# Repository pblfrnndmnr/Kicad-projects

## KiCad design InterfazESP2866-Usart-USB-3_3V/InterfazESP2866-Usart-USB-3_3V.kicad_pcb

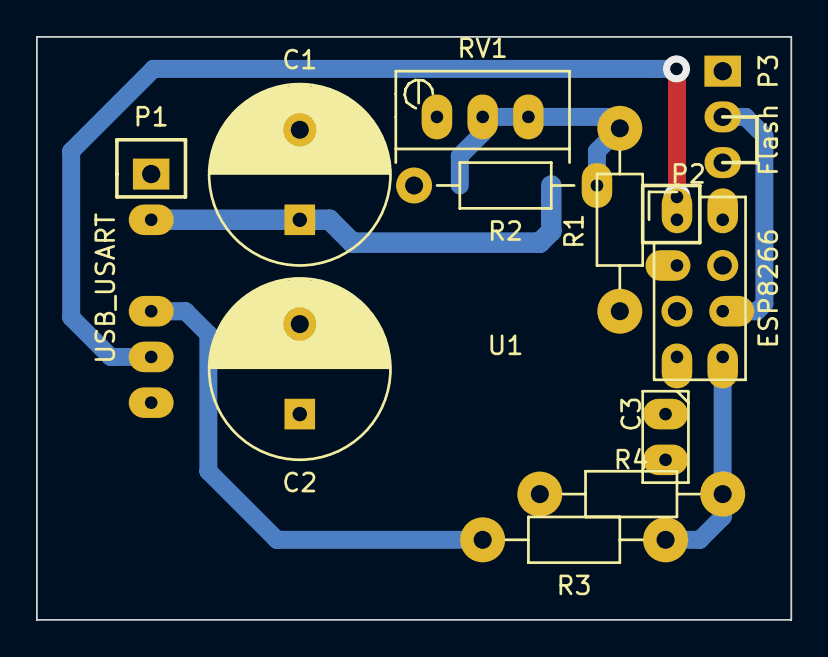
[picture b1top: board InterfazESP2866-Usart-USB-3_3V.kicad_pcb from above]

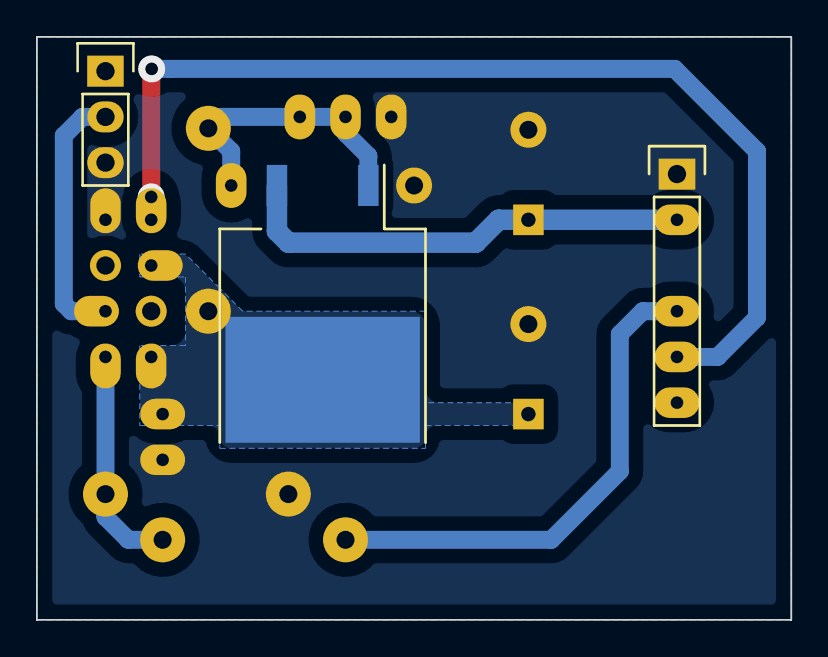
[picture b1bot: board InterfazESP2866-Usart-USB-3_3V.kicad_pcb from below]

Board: 2 copper layers, 41.9 x 32.4 mm, 12 parts (3 on the bottom side), 8 nets.

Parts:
C1: 10uF; C_Radial_D10_L13_P5
C2: 100uF; C_Radial_D10_L13_P5
C3: 100nF; C1
P1: USB_USART; Pin_Header_Straight_1x06
P2: ESP8266; Pin_Header_Straight_2x04
P3: Flash; Pin_Header_Straight_1x03
R1: 120; Resistor_Horizontal_RM10mm
R2: 330; Resistor_Horizontal_RM10mm
R3: 1k; Resistor_Horizontal_RM10mm
R4: 2k; Resistor_Horizontal_RM10mm
RV1: 1k; Potentiometer_Bourns_3296W_3-8Zoll_Inline_ScrewUp
U1: LM1084IS-ADJ/NOPB; TO-263-PadOut

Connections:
/CH_PD: C2.1, C3.1, P2.3, P2.7, R1.1, U1.2
/GPIO0: P2.6, P3.2
/RX: P2.8, R3.2, R4.1
/RXD_USB: P1.5, P2.1
/TXD_USB: P1.4, R3.1
/VCC_USB: C1.1, P1.2, U1.3
GND: C1.2, C2.2, C3.2, P1.1, P2.2, P3.3, R2.2, R4.2, RV1.1
unnamed: R1.2, R2.1, RV1.2, RV1.3, U1.1

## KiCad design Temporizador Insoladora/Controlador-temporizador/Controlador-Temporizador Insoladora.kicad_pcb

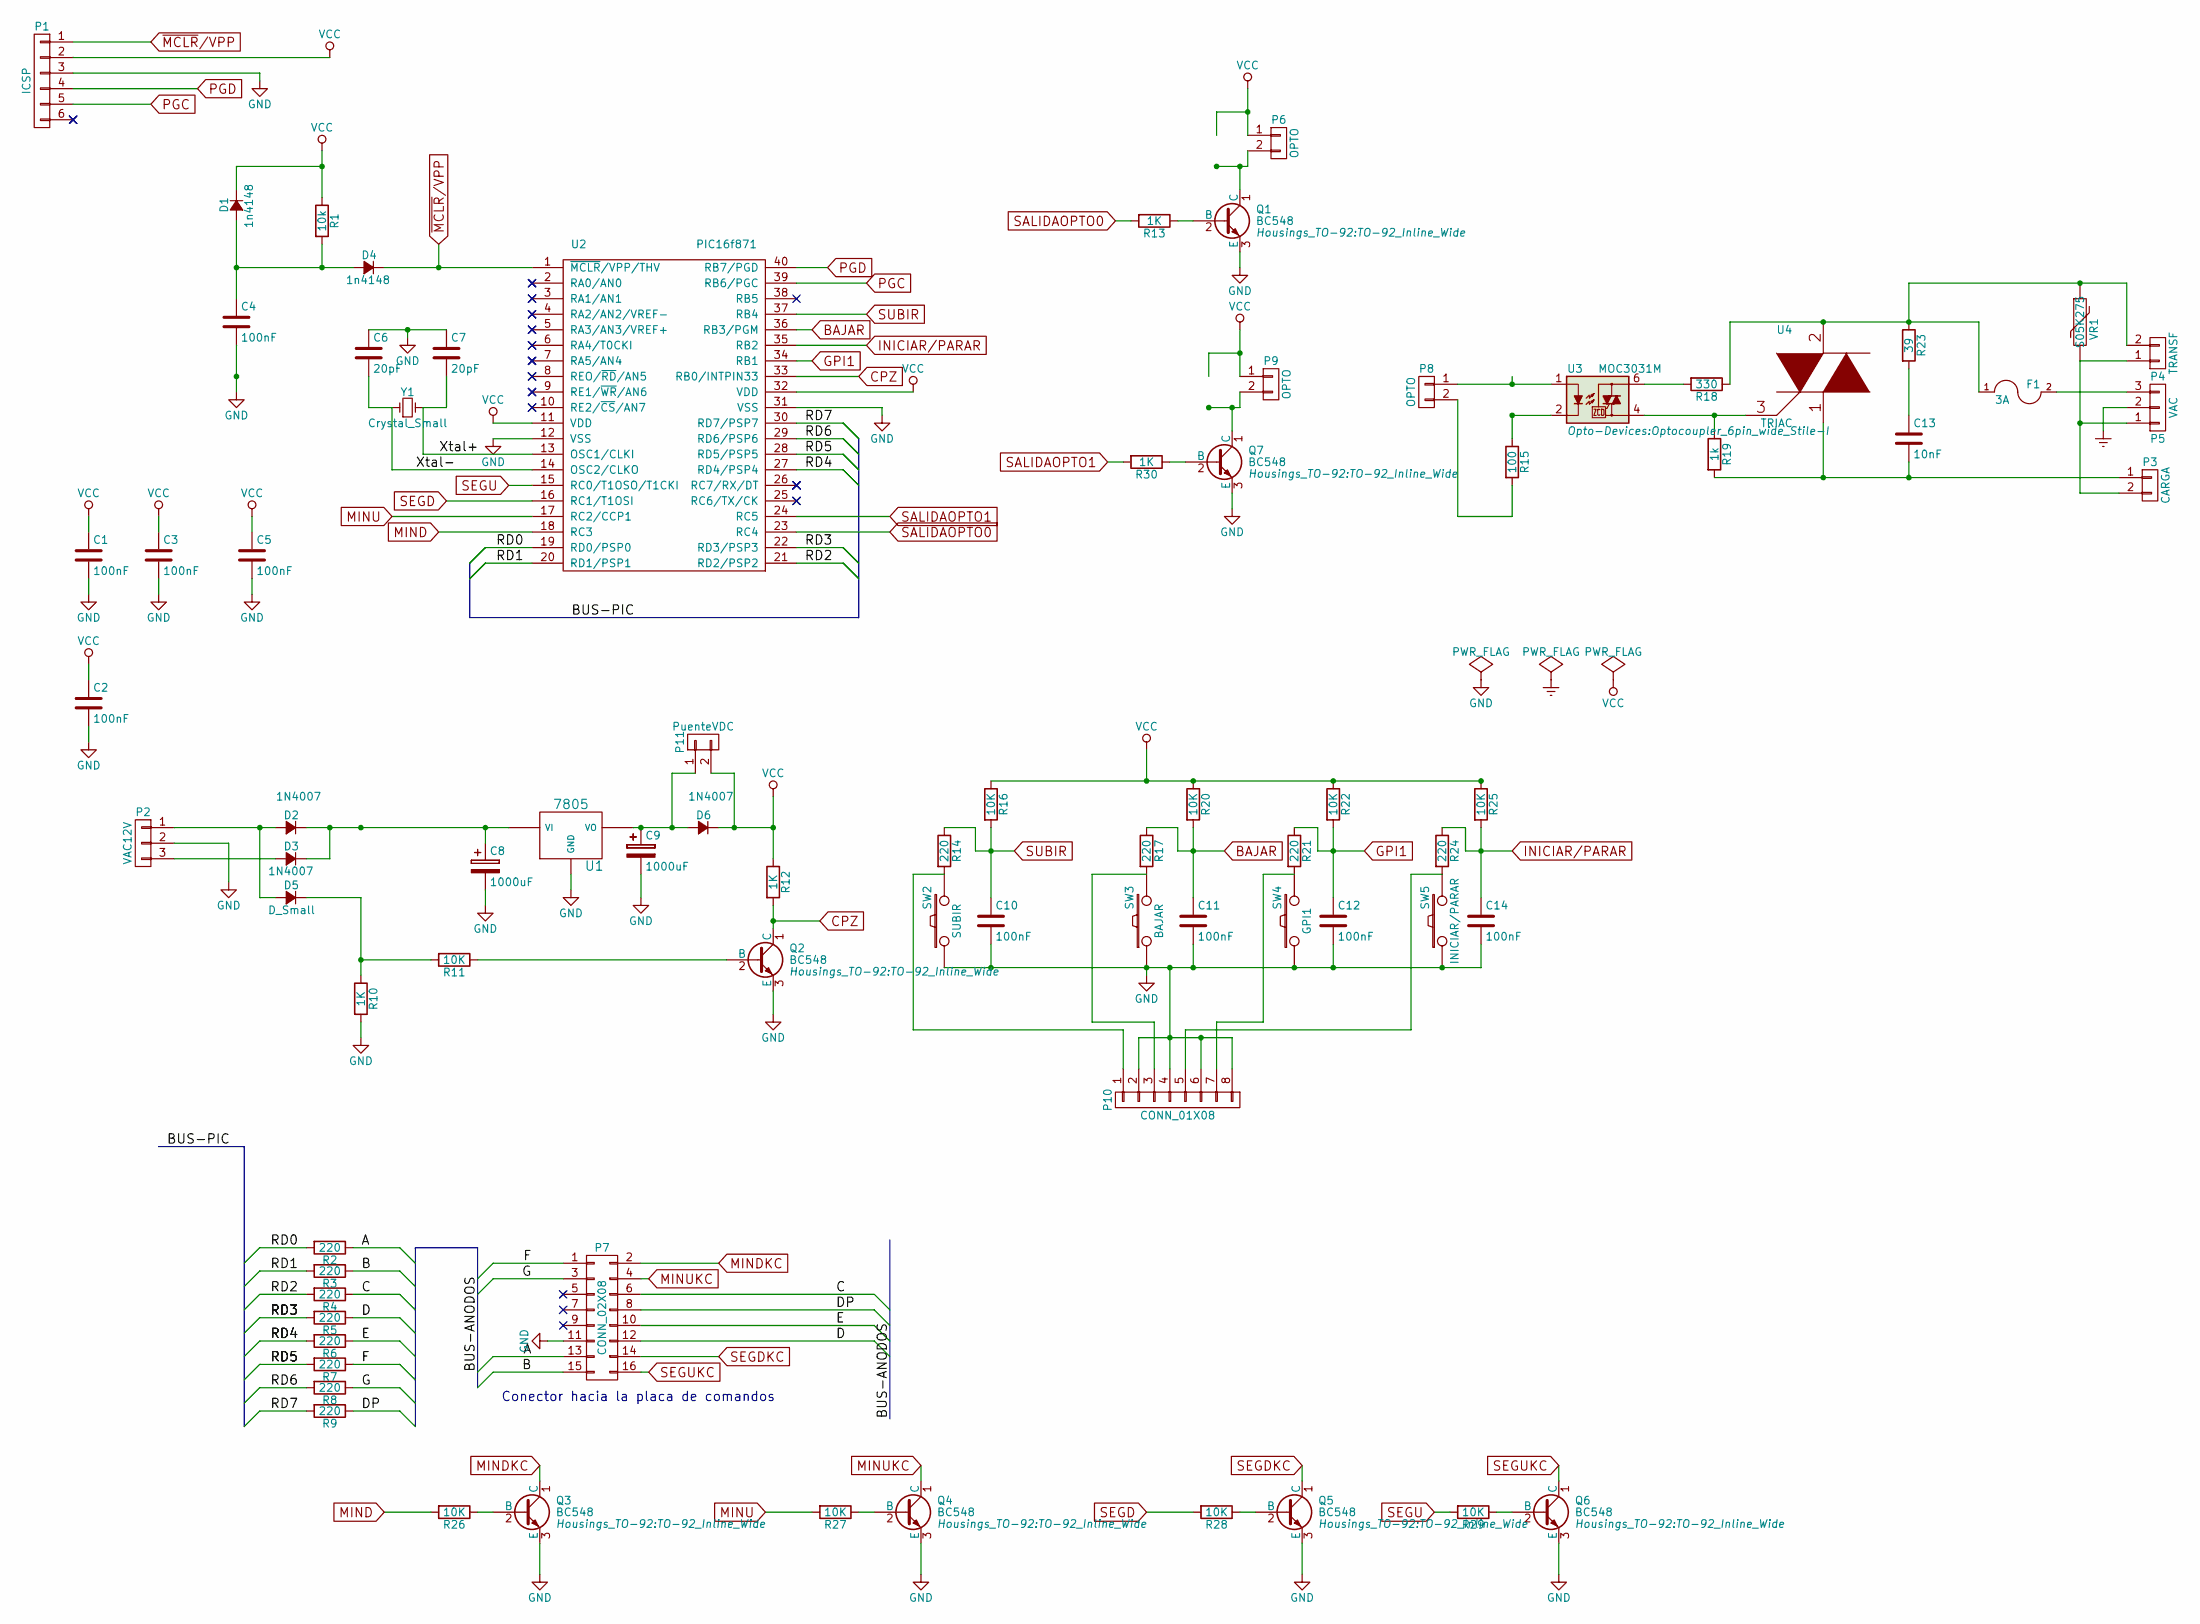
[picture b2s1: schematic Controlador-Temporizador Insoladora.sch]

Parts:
C1, C2, C3, C4, C5, C10, C11, C12, C14: 100nF; C_Rect_L4_W2.5_P2.5
C6, C7: 20pF; C_Rect_L4_W2.5_P2.5
C8, C9: 1000uF; C_Radial_D10_L16_P5
C13: 10nF; C_Rect_L13_W4_P10
D1, D4: 1n4148; Diode_DO-41_SOD81_Horizontal_RM10
D2, D3, D6: 1N4007; Diode_DO-41_SOD81_Horizontal_RM10
D5: D_Small; Diode_DO-41_SOD81_Horizontal_RM10
F1: 3A; Fuseholder5x20_horiz_open_lateral_Type-II
P1: ICSP; Pin_Header_Straight_1x06
P2: VAC12V; bornier3
P3: CARGA; bornier2
P4: TRANSF; bornier2
P5: VAC; bornier3
P6, P8, P9: OPTO; bornier2
P7: CONN_02X08; Socket_Strip_Straight_2x08
P10: CONN_01X08; Socket_Strip_Straight_1x08
P11: PuenteVDC; Socket_Strip_Straight_1x02
Q1, Q2, Q3, Q4, Q5, Q6, Q7: BC548; TO-92_Inline_Wide
R1: 10k; R3
R2, R3, R4, R5, R6, R7, R8, R9, R14, R17, R21, R24: 220; R3
R10, R12, R13, R30: 1K; R3
R11, R16, R20, R22, R25, R26, R27, R28, R29: 10K; R3
R15: 100; R3
R18: 330; R3
R19: 1k; R3
R23: 39; R3
SW2: SUBIR; SW_PUSH_SMALL
SW3: BAJAR; SW_PUSH_SMALL
SW4: GPI1; SW_PUSH_SMALL
SW5: INICIAR/PARAR; SW_PUSH_SMALL
U1: 7805; LM78XXV
U2: PIC16f871; DIP-40__600
U3: MOC3031M; Optocoupler_6pin_wide_Stile-I
U4: TRIAC; TO-220_Neutral123_Horizontal_LargePads
VR1: S05K275; C_Rect_L13_W4_P10
Y1: Crystal_Small; Crystal_HC50-U_Vertical

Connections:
/A: P7.13, R2.1
/B: P7.15, R3.1
/C: P7.6, R4.1
/D: P7.12, R5.1
/DP: P7.8, R9.1
/E: P7.10, R6.1
/F: P7.1, R7.1
/G: P7.3, R8.1
/RD0: R2.2, U2.19 (RD0/PSP0)
/RD1: R3.2, U2.20 (RD1/PSP1)
/RD2: R4.2, U2.21 (RD2/PSP2)
/RD3: R5.2, U2.22 (RD3/PSP3)
/RD4: R6.2, U2.27 (RD4/PSP4)
/RD5: R7.2, U2.28 (RD5/PSP5)
/RD6: R8.2, U2.29 (RD6/PSP6)
/RD7: R9.2, U2.30 (RD7/PSP7)
/Xtal+: C7.2, U2.13 (OSC1/CLKI), Y1.2
/Xtal-: C6.2, U2.14 (OSC2/CLKO), Y1.1
BAJAR: C11.1, R17.1, R20.2, U2.36 (RB3/PGM)
CPZ: Q2.1 (C), R12.2, U2.33 (RB0/INTPIN33)
Earth: P5.2
GND: C1.2, C2.2, C3.2, C4.2, C5.2, C6.1, C7.1, C8.2, C9.2, C10.2, C11.2, C12.2, C14.2, P1.3, P2.2, P7.11, P10.2, P10.4, P10.6, P10.8, Q1.3 (E), Q2.3 (E), Q3.3 (E), Q4.3 (E), Q5.3 (E), Q6.3 (E), Q7.3 (E), R10.2, SW2.1, SW3.1, SW4.1, SW5.1, U1.GND, U2.12 (VSS), U2.31 (VSS)
GPI1: C12.1, R21.1, R22.2, U2.34 (RB1)
INICIAR/PARAR: C14.1, R24.1, R25.2, U2.35 (RB2)
MIND: R26.2, U2.18 (RC3)
MINDKC: P7.2, Q3.1 (C)
MINU: R27.2, U2.17 (RC2/CCP1)
MINUKC: P7.4, Q4.1 (C)
unnamed: C4.1, D1.1 (A), D4.1 (A), R1.2
unnamed: C8.1, D2.2 (C), D3.2 (C), U1.VI
unnamed: C9.1, D6.1 (A), P11.1, U1.VO
unnamed: C13.1, R23.2
unnamed: C13.2, P3.1, R19.2, U4.1
unnamed: D2.1 (A), D5.1 (A), P2.1
unnamed: D3.1 (A), P2.3
unnamed: D5.2 (C), R10.1, R11.2
unnamed: F1.1, P4.2, R18.1, R23.1, U4.2, VR1.1
unnamed: F1.2, P5.3
unnamed: P3.2, P4.1, P5.1, VR1.2
unnamed: P6.2, Q1.1 (C)
unnamed: P8.1, U3.1
unnamed: P8.2, R15.2
unnamed: P9.2, Q7.1 (C)
unnamed: P10.1, R14.2, SW2.2
unnamed: P10.3, R17.2, SW3.2
unnamed: P10.5, R24.2, SW5.2
unnamed: P10.7, R21.2, SW4.2
unnamed: Q1.2 (B), R13.1
unnamed: Q2.2 (B), R11.1
unnamed: Q3.2 (B), R26.1
unnamed: Q4.2 (B), R27.1
unnamed: Q5.2 (B), R28.1
unnamed: Q6.2 (B), R29.1
unnamed: Q7.2 (B), R30.1
unnamed: R15.1, U3.2
unnamed: R18.2, U3.6
unnamed: R19.1, U3.4, U4.3
PGC: P1.5, U2.39 (RB6/PGC)
PGD: P1.4, U2.40 (RB7/PGD)
SALIDAOPTO0: R13.2, U2.23 (RC4)
SALIDAOPTO1: R30.2, U2.24 (RC5)
SEGD: R28.2, U2.16 (RC1/T1OSI)
SEGDKC: P7.14, Q5.1 (C)
SEGU: R29.2, U2.15 (RC0/T1OSO/T1CKI)
SEGUKC: P7.16, Q6.1 (C)
SUBIR: C10.1, R14.1, R16.2, U2.37 (RB4)
VCC: C1.1, C2.1, C3.1, C5.1, D1.2 (C), D6.2 (C), P1.2, P6.1, P9.1, P11.2, R1.1, R12.1, R16.1, R20.1, R22.1, R25.1, U2.11 (VDD), U2.32 (VDD)
~MCLR~/VPP: D4.2 (C), P1.1, U2.1 (~MCLR~/VPP/THV)

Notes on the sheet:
Conector hacia la placa de comandos

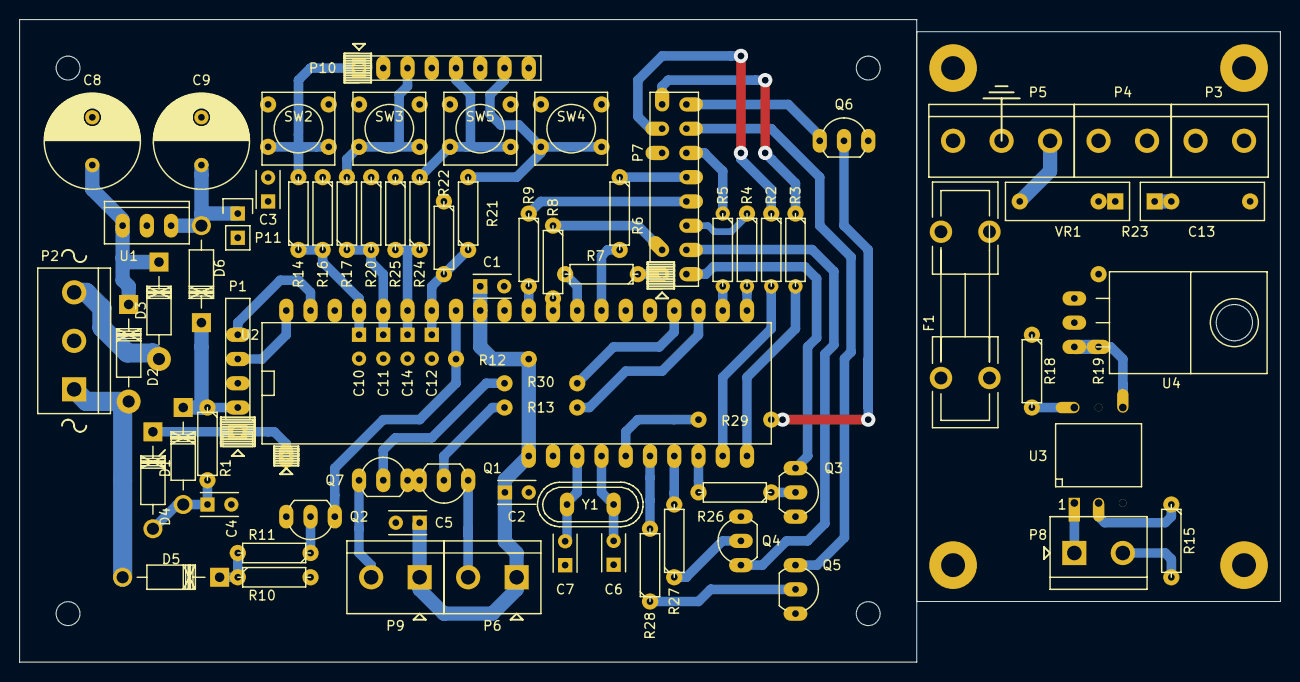
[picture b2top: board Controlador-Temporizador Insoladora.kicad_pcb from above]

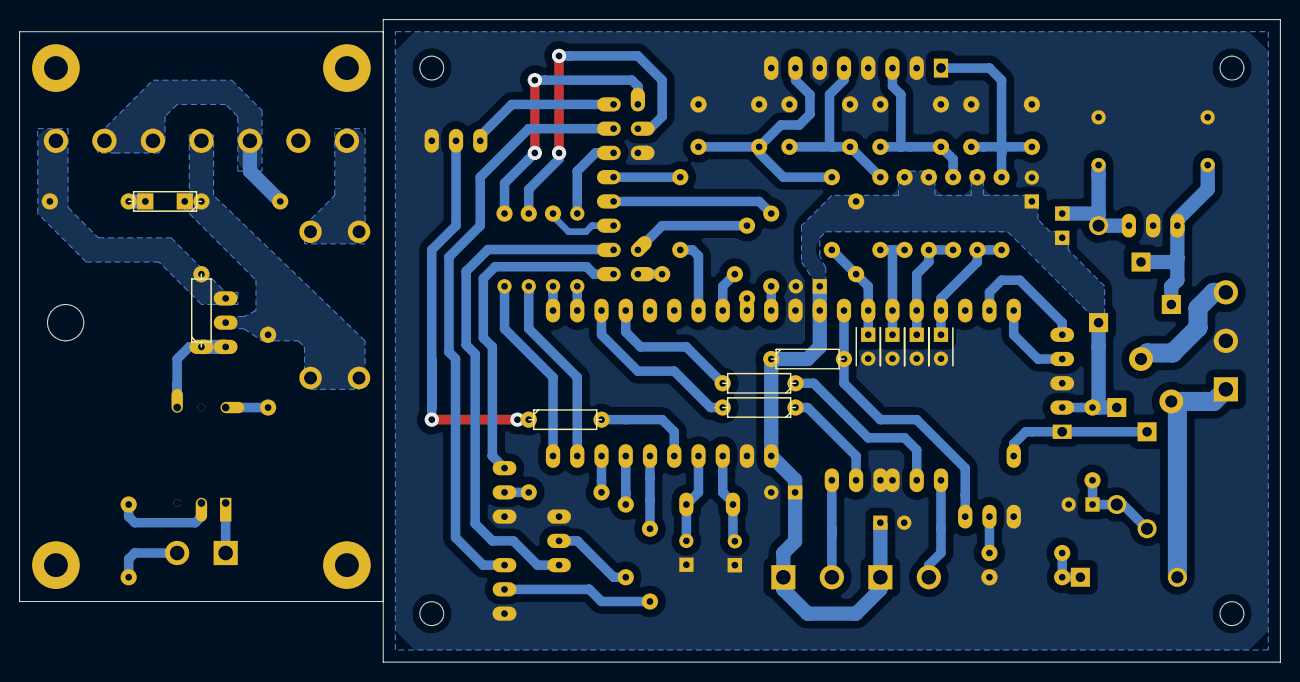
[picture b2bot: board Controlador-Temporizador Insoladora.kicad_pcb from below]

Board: 2 copper layers, 132.1 x 67.3 mm, 79 parts (10 on the bottom side), 67 nets.

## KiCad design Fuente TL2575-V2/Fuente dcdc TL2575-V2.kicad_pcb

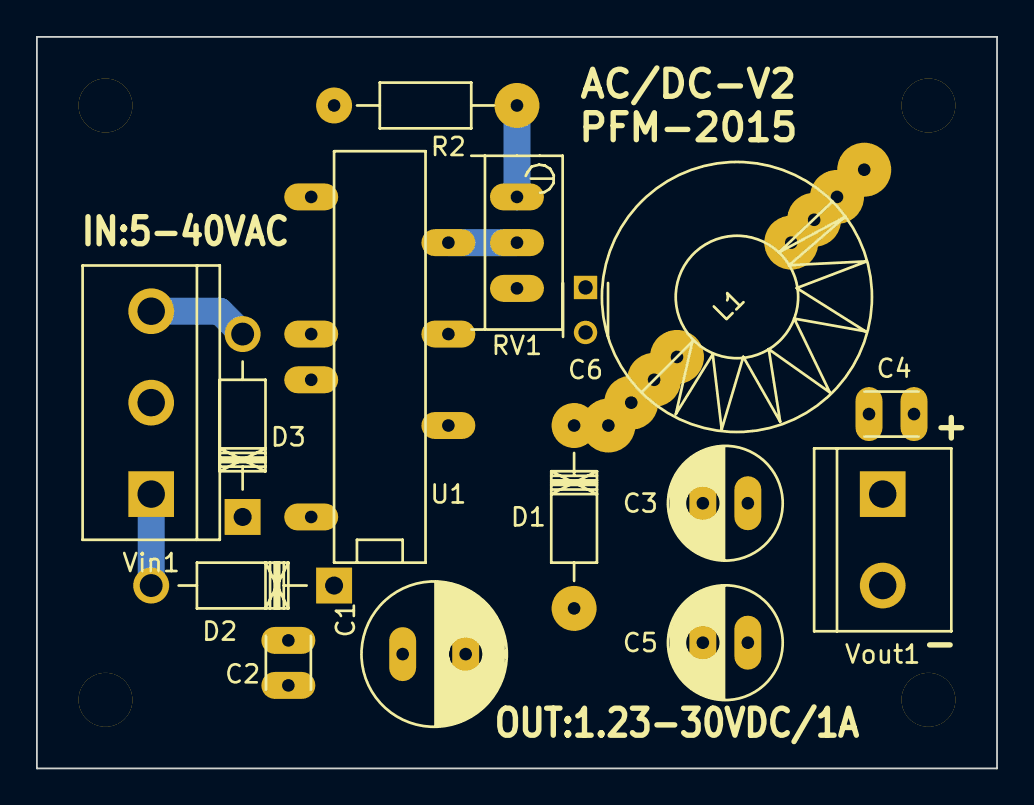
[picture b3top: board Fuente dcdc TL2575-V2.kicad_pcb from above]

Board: 2 copper layers, 53.3 x 40.6 mm, 15 parts (0 on the bottom side), 8 nets.

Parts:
C1: 3300uF; C_Radial_D8_L11.5_P3.5
C2, C4, C6: 100nF; C_Disc_D3_P2.5
C3, C5: 100uF; C_Radial_D6.3_L11.2_P2.5
D1: D_Schottky; Diode_DO-41_SOD81_Horizontal_RM10
D2, D3: D; Diode_DO-41_SOD81_Horizontal_RM10
L1: 220uH; Choke_Toroid_horizontal_Diameter14mm_Amidon-T50
R2: R; Resistor_Horizontal_RM10mm
RV1: POT; Potentiometer_Bourns_3296W_3-8Zoll_Inline_ScrewUp
U1: TL2575; DIP-16__300_ELL
Vin1: VIN; bornier3
Vout1: VOUT; bornier2

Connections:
GND: C1.2, C2.2, C3.2, C4.2, C5.2, C6.2, D1.1, R2.2, U1.5, U1.9, U1.12, U1.13, Vin1.2, Vout1.2
unnamed: C1.1, C2.1, D2.2, D3.2, U1.16
unnamed: C3.1, C4.1, C5.1, C6.1, L1.2, RV1.3, Vout1.1
unnamed: D1.2, L1.1, U1.3
unnamed: D2.1, Vin1.1
unnamed: D3.1, Vin1.3
unnamed: R2.1, RV1.1
unnamed: RV1.2, U1.7

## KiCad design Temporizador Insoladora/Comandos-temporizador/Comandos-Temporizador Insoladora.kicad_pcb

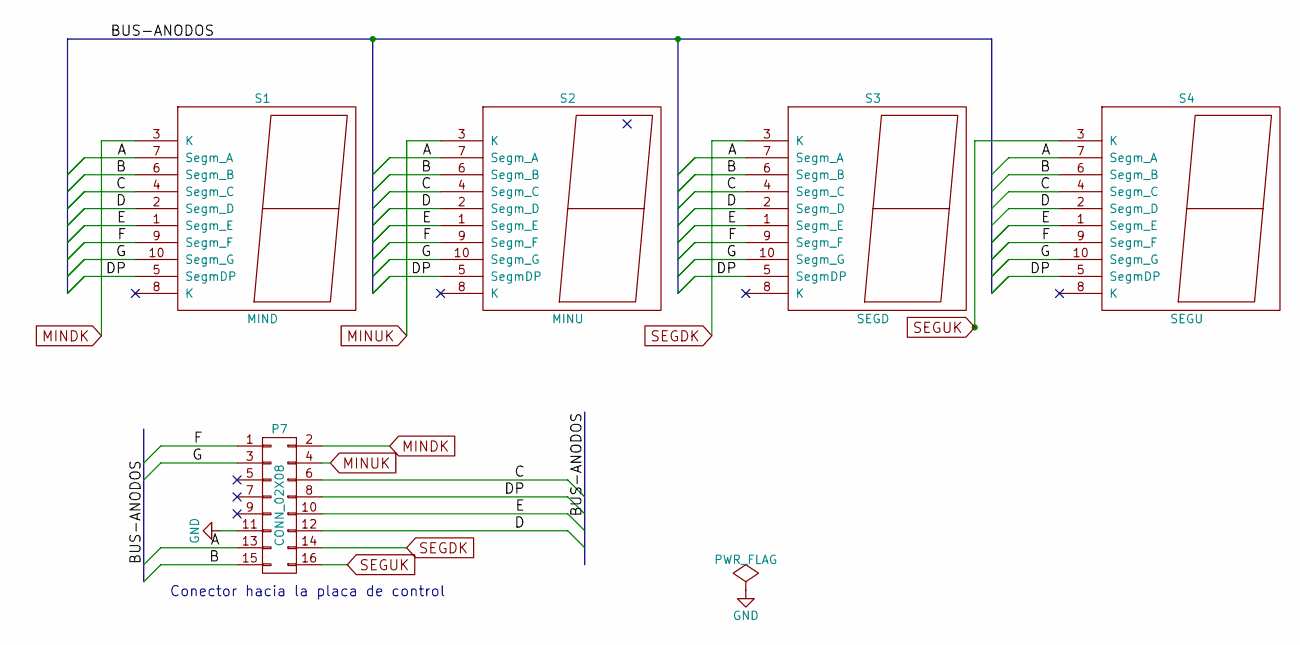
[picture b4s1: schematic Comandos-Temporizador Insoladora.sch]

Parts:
P7: CONN_02X08; Pin_Header_Straight_2x08
S1: MIND; 7SegmentLED_LTS6760_LTS6780
S2: MINU; 7SegmentLED_LTS6760_LTS6780
S3: SEGD; 7SegmentLED_LTS6760_LTS6780
S4: SEGU; 7SegmentLED_LTS6760_LTS6780

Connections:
/A: P7.13, S1.7 (Segm_A), S2.7 (Segm_A), S3.7 (Segm_A), S4.7 (Segm_A)
/B: P7.15, S1.6 (Segm_B), S2.6 (Segm_B), S3.6 (Segm_B), S4.6 (Segm_B)
/C: P7.6, S1.4 (Segm_C), S2.4 (Segm_C), S3.4 (Segm_C), S4.4 (Segm_C)
/D: P7.12, S1.2 (Segm_D), S2.2 (Segm_D), S3.2 (Segm_D), S4.2 (Segm_D)
/DP: P7.8, S1.5 (SegmDP), S2.5 (SegmDP), S3.5 (SegmDP), S4.5 (SegmDP)
/E: P7.10, S1.1 (Segm_E), S2.1 (Segm_E), S3.1 (Segm_E), S4.1 (Segm_E)
/F: P7.1, S1.9 (Segm_F), S2.9 (Segm_F), S3.9 (Segm_F), S4.9 (Segm_F)
/G: P7.3, S1.10 (Segm_G), S2.10 (Segm_G), S3.10 (Segm_G), S4.10 (Segm_G)
GND: P7.11
MINDK: P7.2, S1.3 (K)
MINUK: P7.4, S2.3 (K)
SEGDK: P7.14, S3.3 (K)
SEGUK: P7.16, S4.3 (K)

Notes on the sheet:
Conector hacia la placa de control

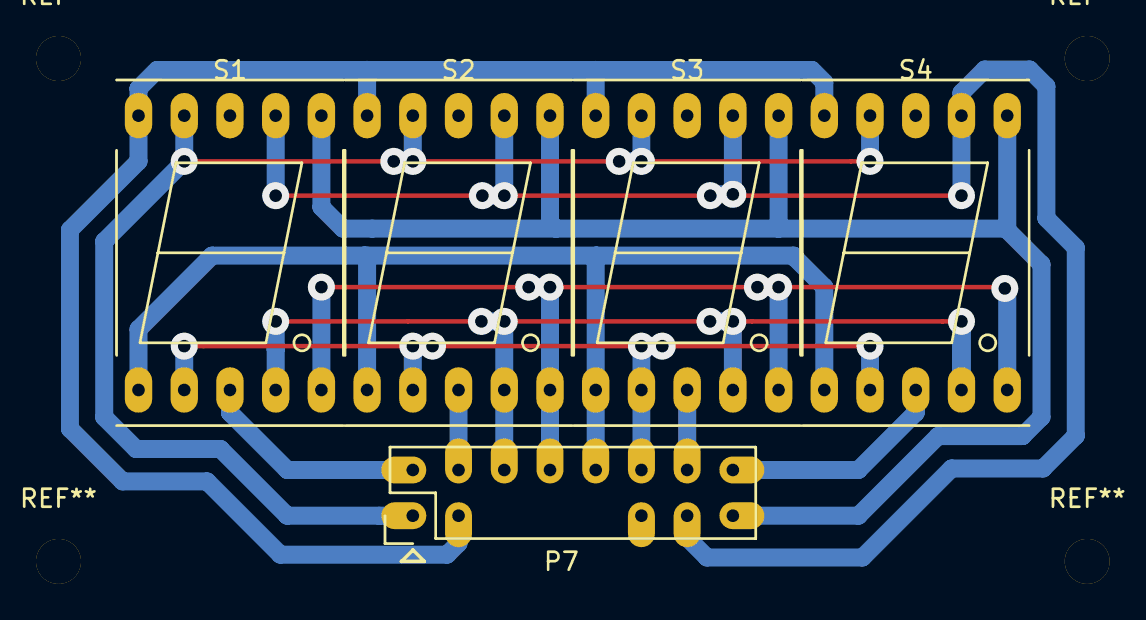
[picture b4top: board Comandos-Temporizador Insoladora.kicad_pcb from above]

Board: 2 copper layers, 5 parts (0 on the bottom side), 12 nets.

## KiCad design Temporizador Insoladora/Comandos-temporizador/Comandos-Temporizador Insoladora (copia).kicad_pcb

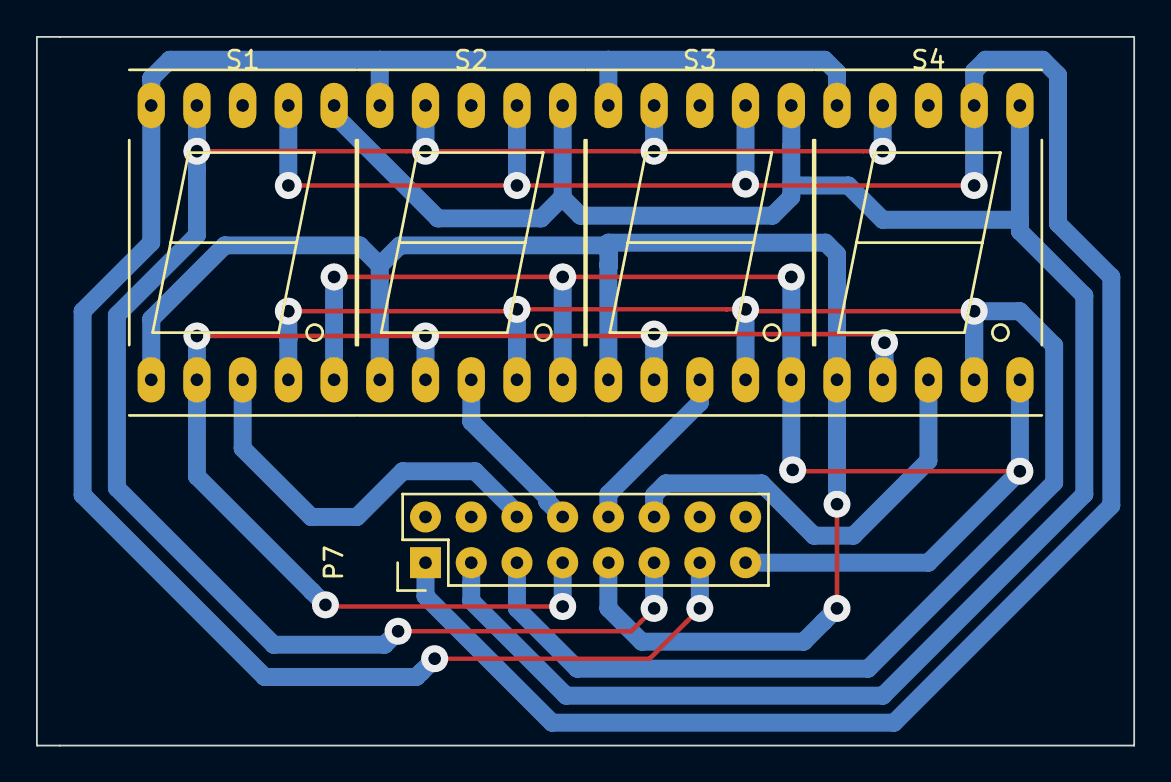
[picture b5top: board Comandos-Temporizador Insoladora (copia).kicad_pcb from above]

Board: 2 copper layers, 61.0 x 39.4 mm, 5 parts (0 on the bottom side), 12 nets.

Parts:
P7: CONN_02X08; Pin_Header_Straight_2x08
S1: MIND; 7SegmentLED_LTS6760_LTS6780
S2: MINU; 7SegmentLED_LTS6760_LTS6780
S3: SEGD; 7SegmentLED_LTS6760_LTS6780
S4: SEGU; 7SegmentLED_LTS6760_LTS6780

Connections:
/A: P7.1, S1.7, S2.7, S3.7, S4.7
/B: P7.3, S1.6, S2.6, S3.6, S4.6
/C: P7.5, S1.4, S2.4, S3.4, S4.4
/D: P7.7, S1.2, S2.2, S3.2, S4.2
/DP: P7.15, S1.5, S2.5, S3.5, S4.5
/E: P7.9, S1.1, S2.1, S3.1, S4.1
/F: P7.11, S1.9, S2.9, S3.9, S4.9
/G: P7.13, S1.10, S2.10, S3.10, S4.10
MINDK: P7.6, S1.3
MINUK: P7.8, S2.3
SEGDK: P7.10, S3.3
SEGUK: P7.12, S4.3

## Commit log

2015-04-21 primer subida al repositorio
2015-04-21 nada
2015-04-21 borrando archivos innecesarios
2015-04-22 Comienzo a diseñar el controlador
2015-04-23 Comienzo ruteo controlador insoladora
2015-04-23 Sigo ruteando pcb controlador insoladora
2015-04-24 Sigo ruteando controlador
2015-04-24 Acomodando el controlador
2015-04-25 Agregada libreria
2015-04-26 Arregladas librerias
2015-04-27 Acomodando librerias en fuente tl2575
2015-04-28 Ruteando controlador
2015-04-29 Ruteando Controlador ver si hay que modificar algo en el esquemático
2015-04-29 Ruteando controlador. Debo separar la parte de potencia de la parte de control para evitar problemas con las tensiones. y adaptar el circuito para usar un triac o un relé de 5V
2015-04-30 Sigo ruteando controlador, se separa en dos placas la parte de potencia de la de control
2015-04-30 Sigo ruteando, falta poco
2015-04-30 Casi terminado
2015-05-01 Va queriendo
2015-05-01 Ruteo casi terminado
2015-05-01 casi terminado el ruteado de la placa controlador
2015-05-03 Sigo ruteando el controlador
2015-05-11 Acomodando ruteo y componentes de pcb controlador
2015-05-13 Sigo acomodando controlador
2015-05-14 Quitado pulsador de reset por ser irrelevante para la aplicación
2015-05-18 Reacomodando controlador
2015-05-18 Acomodando controlador
2015-05-18 Cambio del lugar donde se detecta el cruce por cero
2015-05-19 Casi terminado controlador
2015-05-20 Acomodando la parte de potencia del controlador
2015-05-20 Casi termonado controlador, ver si los componentes se ajustan
2015-05-21 Controlador finalizado
2015-05-21 Primer prueba de impresion de fotolitos
2015-05-21 Cambiado tamaño de footprint del capacitor y varistor de la parte de potencia
2015-05-22 Acomodando las referencias de los compònentes para el top silk
2015-05-22 Quitando los puentes innecesarios del pcb. Cambio del lugar del diodo de entrada para hacer compatible con el ICSP
2015-05-23 Agregado plano de masa al display
2015-05-23 Agrandado de pads en footprint de algunos componentes
2015-05-23 Terminada controlador
2015-05-24 Solo retoques en el pcb
2015-05-24 Reacomodando componentes y tamaño de placas del controlador
2015-05-25 Cambiado footprint del triac controlador. Placa controlador teminada. Placa Comandos terminada
2015-05-26 Placa controlador teminada. Placa Comandos terminada
2015-05-27 Terminada Fuente TL2575, y controlador
2015-05-27 Para imprimir, fuente TL2575 y Controlador
2015-05-28 Se realizó la segunda versión de la fuente TL2575
2015-05-29 Modificando la version 2 de la fuente TL2575
2015-05-29 Finalizando TL2575-V2
2015-06-02 Modificacxiones meores a la fuente TL2575 V2
2015-06-19 No mucho
2015-06-24 Nada nuevo
2015-07-22 Diseño de interfaz usb con 18f4550
2015-07-30 Avanzando en interfaz 18f4550
2015-08-25 Diseñando una interfaz para conversor usb-usart hacia el esp8266 y un regulador LDO variable ajustado en 3.3V
2015-08-29 Cambios menores en interfaz usb
2015-08-31 Terminado de rutear interfaz usart usb
